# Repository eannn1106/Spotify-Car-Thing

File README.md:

# Spotify Car Thing_v1
A designated spotify display that can control playback, fetch track information including song duration, song artist, song album and displays lyrics. This spotify display is specially modified to fit in among non-coders by logging in wifi credentials throughout captive portal.
However for the one-time authentication part from Spotify API have to done it through a serial monitor by running the given code. 

****Note this device requires Spotify Premium and external sound system e.g. phone, laptop, speaker**

# Why I want to build this?
- A spotify car thing manufactured from Spotify costs over 30 USD, and for aesthetics reasons, I think that it is cool to have one sitting right in front of the car dashboard.
- The original spotify car thing doesn't support lyrics display and whenever I heard a song playing in my Spotify, I have the curiosity to seek for the lyrics. But I doesn't want the lyrics to pop out in the corner of my desktop. Instead I wanted a seperate display device for this.
- Spotify discontinued their Car Thing in 2022 which then I think there is a lot of potential with this product it can bring to the car interior industry and music industry.
# Why you should prefer this and not other products?
- Cheap and affordable. Products like this only uses microcontrollers to access the API through internet to get lyrics and fetch track information and display it through a friendly budget display screen.
- Doesn't have to be a "car thing", it can be a display on your table for decorating purposes.
- Flexibility. Instead of using bluetooth, this device requires wifi which is much more wider and higher bandwidth compared to bluetooth.
- Low power required. This device only borrows a little port from your device to operate, and doesn't requires a power plug for this device to work.
# How to setup? (one-time setup)
1. Download the sketch file code into Arduino IDE or other code editor platforms that support sketch files.
2. Go to https://developer.spotify.com/dashboard and click create apps to have access to the API.
3. For the redirect url, enter this url https://spotifyesp32.vercel.app/api/spotify/callback
4. Copy the client ID and client secret in the developer page.
**image from developer.spotify.com
5. Enter the client ID and client secret at the 16th and 17th row.
6. Plug in the Spotify Car Thing into your laptop or desktop.
7. Compile and upload the code into the esp32 devkit_v1.
8. Open the serial monitor.
9. Connect to the wifi called "SpotifyCarThing" with the password "spotify123".
10. It will bring you to a captive web portal for you to enter your wifi credentials. 
11. Enter your wifi credentials in the text box, it can be a home wifi or your personal hotspot from your device. (the wifi have to be in 2.4 GHz Band) **(IOS user have to turn on maximise compatibility)**
12. From the serial monitor, copy the authentication url provided and copy it into your browser to login and authenticate your spotify account. 
13. Play something on your Spotify app!
# How to use it (in the long run)
1. Powering it up
   - Connect this to a 5v power supply through the micro usb slot in the left hand side of the device. A USB port from your laptop/desktop or a standard 5v USB wall charger will do.
2. Play/Pause toggle switch
   - Locate the middle from top to bottom switch to play or pause the current track.
3. Skip track switch
   - Locate the most bottom from top to bottom switch to skip forward the current playing track.
4. Previous track switch
   - Locate the toppest from top to bottom switch to skip backwards the current playing track.
5. Reset WiFi hidden switch
   - Long press on all 3 switch for 3 seconds the reset the WiFi.
   - Repeat the process to enter wifi credentials
# How it works
1. Authentication mode

 **image from developer.spotify.com

- Refresh token is the permanent credential while access token expires every hour but Spotify ESP32 library handles renewal automatically.
- Spotify ESP32 library will generate an authentication url with random state tokens that cant be duplicated and print it in the serial monitor.
- After authentication, spotify redirects to vercel.app callback which also handled by spotify ESP32 library.
- Callback exchanges authentication code for refresh token and access token.
- ESP32 receives these tokens by using this sp.handle_client() function and refresh token will be saved by using SPIFFS library in the flash memory.
2. Controlling playback flow
- By setting the scopes from https://developer.spotify.com/documentation/web-api/concepts/scopes, it allows us to make a few requests to spotify api and obtain information, for this specific project I've set the scopes to user-read-playback-state, user-modify-playback-state and user-read-currently-playing.
- Refresh token is loaded and access token is constantly be renewed by Spotify ESP32 library on first API call.
- API will be called for every 1 second to obtain the real position of the specific track position.
- Obtained data from the web api will be in Json document form and will be parsed into each variable.
3. Obtaining lyrics from lrclib API
- ESP32 will make HTTP requests to obtain the lyrics in Json document form containing synced lyrics and unsynced lyrics.
4. Synced lyrics
- Lrclib API is a free open source lyrics API, and obtained synced lyrics comes with the format of milisecond timestamp where convertions will be handled locally by ESP 32.
- ESP32 will create it's own timestamp to match with the synced lyrics' timestamp whenever the current track started playing.
5. Wifi login
- ESP32 will first check if there is any saved networks in the flash memory, if no it will execute captive portal.
- ESP32 will create a Wifi hotspot "SpotifyCarThing" by switching mode to Access point mode.
- DNSServer intercepts all DNS queries and redirect to the IP address of your ESP32.
- Browser automatically opens the setup page for user to type in their wifi credentials.
- After user types their wifi credentials, it will be saved into the flash memory of ESP32 using the Prefences library.
- ESP32 switches to station mode, and the captive portal will be closed.
- Right now, ESP32 will already have the saved wifi credentials in their flash memory, ESP32 will restart and check then connects to the wifi in the flash memory.
6. TFT display management
- Rewriting the entire screen every second will cause constant visible flickering. Instead, each displayed element in NowPlayingInfo is being tracked by the variables locally.
- If the displayed elements doesnt match the current element, it will be updated.
- Text sizing is dynamic as size 2 is used by defauly and will automatically drop the size to 1 if the text is wider than the screen width which is 480px.

# Parts needed
[Bill of Materials](BOM.csv)

# How to assemble?
1. Prepare all the parts stated in the BOM
2. Solder the keyboard switches onto the pcb according to the silkscreen layer.
3. We'll start with attatching the ESP32 into the PCB via the connector sockets.
4. Secure the PCB into the 4 tower screws with 4x 4mm m3 self-tapped screws.
5. Insert and attach the 3.5'' rpi display throgh the hole of the case and into the pcb's connector header pins.
6. Attach the keycaps to the keyboard switch for easier control of buttons.

# Libraries installed
1. Spotify Esp32 - https://github.com/FinianLandes/SpotifyEsp32.git
2. Arduino Json - https://github.com/bblanchon/ArduinoJson.git
3. TFT_eSPI - https://github.com/Bodmer/TFT_eSPI.git

# Schematics

# PCB

3D view of the PCB

To make the device more compact, I decided to add the ESP32 below the PCB.
# Case
The case is being held by 4 cantilever snaps at the four corners of the case.

The PCB is being screwed into these 4 screw towers using 4x M3 screws

I got the inspiration from a retro tv specifically this type.

The case looks boxy and have slight rounded edges on the side but, for the bottom of the case, I won't make it curved as it can't be tumbling down from bumpy roads. The controls are on the right hand side and the screen is on the left hand side of the case.

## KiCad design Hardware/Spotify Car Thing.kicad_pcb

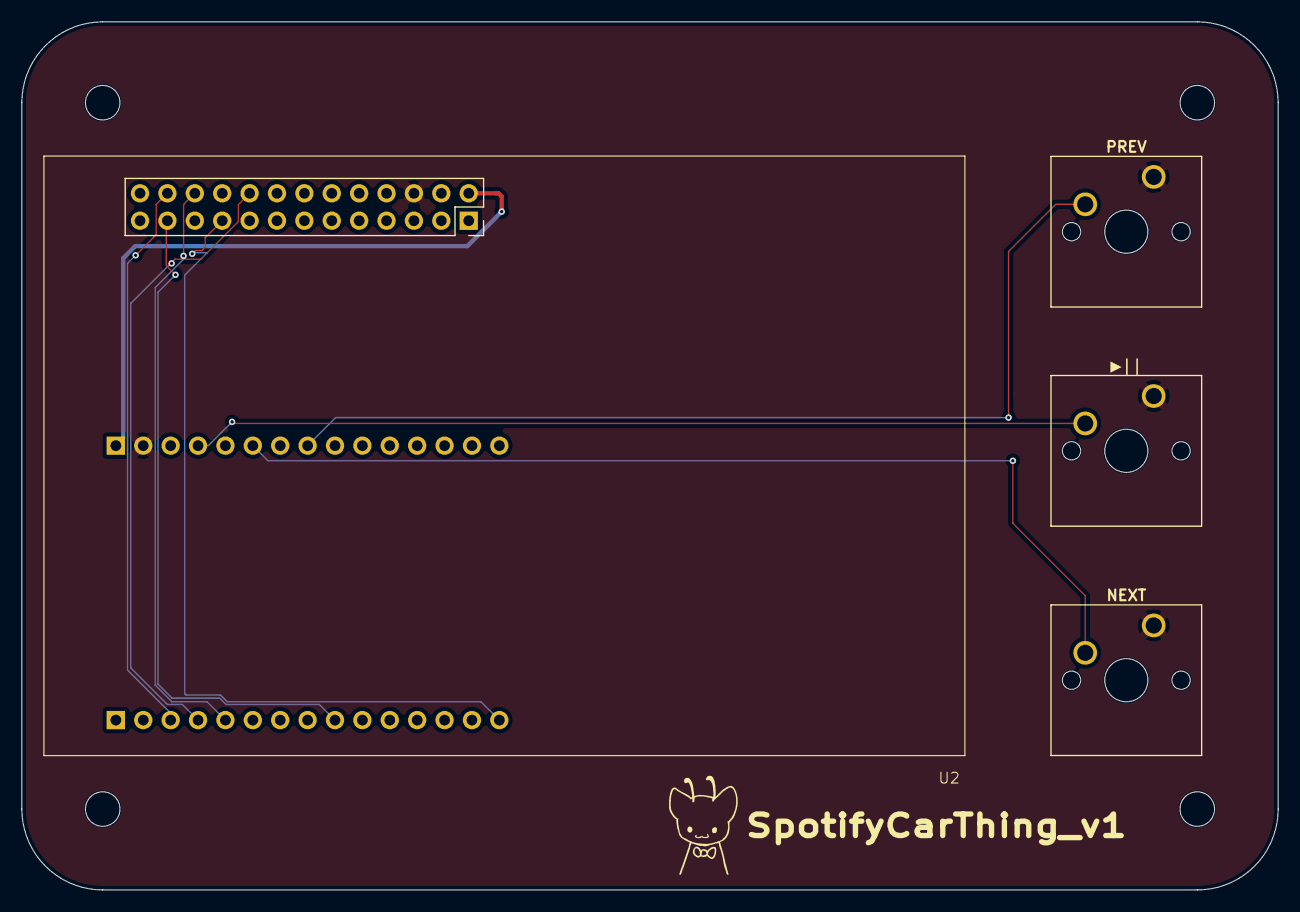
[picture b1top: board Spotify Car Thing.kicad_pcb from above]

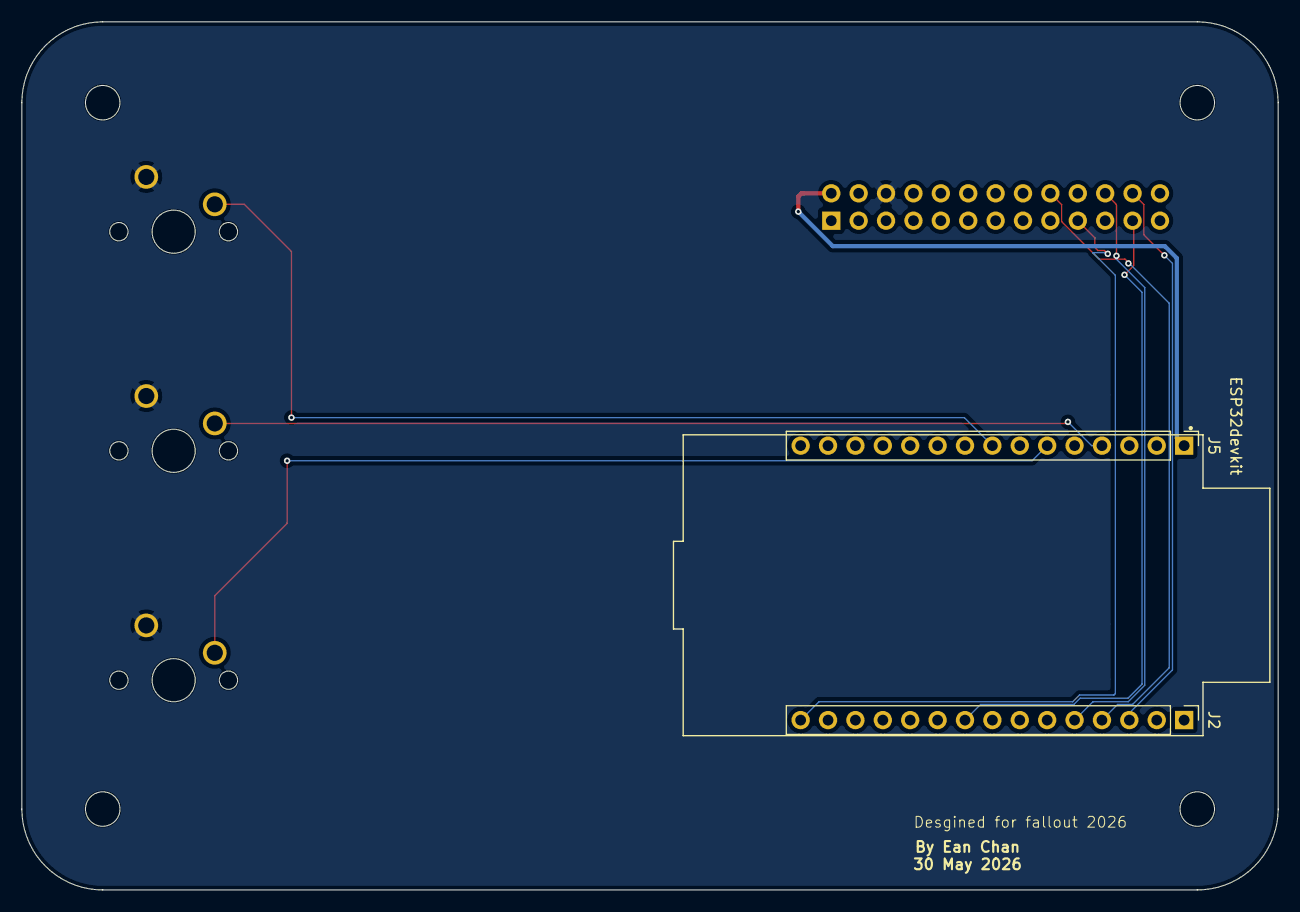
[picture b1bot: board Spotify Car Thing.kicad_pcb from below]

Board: 4 copper layers, 116.5 x 80.5 mm, 8 parts (3 on the bottom side), 10 nets.

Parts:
ESP32devkit: DEVKIT_V1_ESP32-WROOM-32; MODULE_DEVKIT_V1_ESP32-WROOM-32
J1: Conn_01x26_Pin; PinHeader_2x13_P2.54mm_Vertical
J2, J5: Conn_01x15_Socket; PinSocket_1x15_P2.54mm_Vertical
NEXT: SW_Push; SW_Cherry_MX_1.00u_PCB
PREV: SW_Push; SW_Cherry_MX_1.00u_PCB
U2: 3.5'' TFT RPI Display; 3.5'' TFT RPI Screen Display
▶︎||: SW_Push; SW_Cherry_MX_1.00u_PCB

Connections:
+5V: J1.2, J5.1
GND: J1.6, J5.2, NEXT.1, PREV.1, ▶︎||.1
unnamed: J1.18, J2.4
unnamed: J1.19, J2.15
unnamed: J1.22, J2.5
unnamed: J1.23, J2.9
unnamed: J1.24, J2.3
unnamed: J5.4, ▶︎||.2
unnamed: J5.6, NEXT.2
unnamed: J5.8, PREV.2

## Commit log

2026-06-04 README.md
2026-06-04 Create Firmware
2026-06-04 Rename Spotify Car Thing (gerber compressed).zip to Spotify Car Thing (gerber compressed).zip
